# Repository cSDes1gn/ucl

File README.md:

# Automated Under Cabinet Lighting

Modified: 2022-10

Under cabinet lighting (ucl) control system.

## License
This project is licensed under the terms of the [MIT License](LICENSE)

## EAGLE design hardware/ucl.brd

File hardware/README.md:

# EAGLE CAD Files

Modified: 2023-08

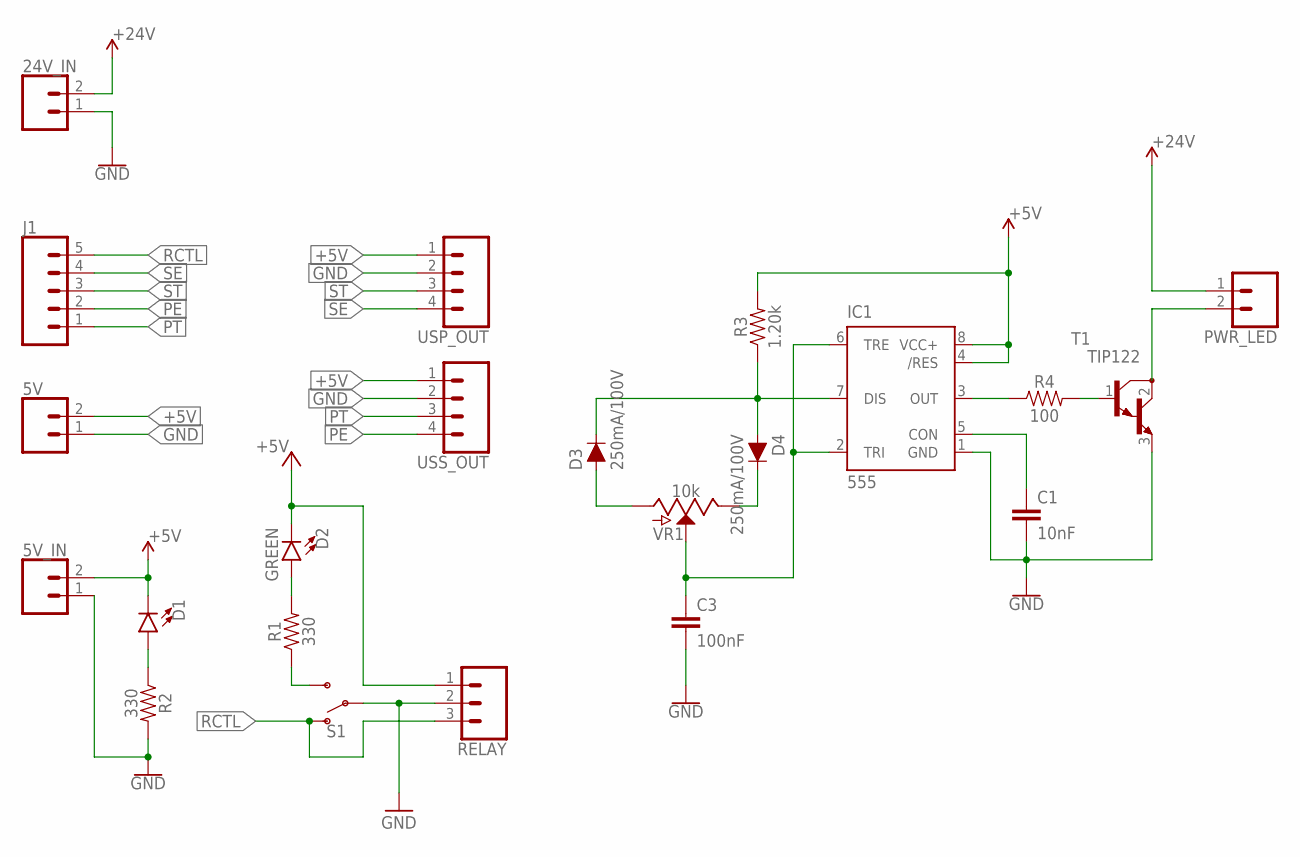
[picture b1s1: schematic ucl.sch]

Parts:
5V: CONN_02POLAR; MOLEX-1X2
5V_IN, 24V_IN: CONN_02POLAR_LOCK; MOLEX-1X2_LOCK
C1: 10nF; 0402-TIGHT
C3: 100nF; 0402-TIGHT
D1: LED1206; LED-1206
D2: GREEN; LED-1206
D3, D4: 250mA/100V; SOD-323
IC1: 555; SO08
J1: CONN_05; 1X05
PWR_LED: CONN_02POLAR_LOCK; MOLEX-1X2_LOCK
R1, R2: 330; 0603
R3: 1.20k; 0603
R4: 100; 0603
RELAY: CONN_03POLAR_LOCK; MOLEX-1X3_LOCK
S1: SWITCH-SPDT-PTH-11.6X4.0MM-KIT; SWITCH_SPDT_PTH_11.6X4.0MM_KIT
T1: TIP122; TO220
USP_OUT: CONN_04POLAR_LOCK; MOLEX-1X4_LOCK
USS_OUT: CONN_04POLAR_LOCK; MOLEX-1X4_LOCK
VR1: 10k; POT-PTH-ALPS

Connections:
+5V: 5V.2, 5V_IN.2, D1.C, D2.C, IC1.4 (/RES), IC1.8 (VCC+), R3.2, RELAY.1, USP_OUT.1, USS_OUT.1
+24V: 24V_IN.2, PWR_LED.1
GND: 5V.1, 5V_IN.1, 24V_IN.1, C1.2, C3.2, IC1.1 (GND), R2.2, RELAY.2, S1.2, T1.3 (E), USP_OUT.2, USS_OUT.2
unnamed: R1.1, S1.3 (S)
unnamed: D2.A, R1.2
unnamed: D1.A, R2.1
unnamed: D3.C, D4.A, IC1.7 (DIS), R3.1
unnamed: D3.A, VR1.P$3 (A)
unnamed: D4.C, VR1.P$1 (E)
unnamed: C3.1, IC1.2 (TRI), IC1.6 (TRE), VR1.P$2 (S)
unnamed: IC1.3 (OUT), R4.1
unnamed: R4.2, T1.1 (B)
unnamed: C1.1, IC1.5 (CON)
unnamed: PWR_LED.2, T1.2 (C)
PE: J1.2, USS_OUT.4
PT: J1.1, USS_OUT.3
RCTL: J1.5, RELAY.3, S1.1 (O)
SE: J1.4, USP_OUT.4
ST: J1.3, USP_OUT.3

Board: 2 copper layers, 22 parts (0 on the bottom side), 19 nets, no tracks yet.

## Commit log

2021-11-01 adding eagle hardware project files
2021-11-01 add arduino src code
2022-09-05 some basic commit
2022-09-06 update gitignore
2022-09-06 c vscode config
2022-09-06 add build and flash instructions
2022-09-06 sample usart program
2022-09-06 use usart 0
2022-09-07 update browse path
2022-09-07 add source file linker
2022-09-07 create first module
2022-09-07 move to include folder
2022-09-07 ignore build artefacts
2022-09-07 basic cmake toolchain for fuse setting and compilation
2022-09-07 updates to firmware
2022-09-07 finish first pass of cmake toolchain development
2022-09-07 fix fuse target
2022-09-09 write basic eeprom driver
2022-09-09 small toolchain fixes
2022-09-09 add guards and fix enable bit checks
2022-09-09 add eeprom test
2022-09-09 hack prints
2022-09-10 add brew installs
2022-09-10 add logger source to toolchain
2022-09-10 adapt merase c logger to work with avr
2022-09-10 deprecate arduino api work
2022-09-10 add usart printlf
2022-09-10 improve function names
2022-09-10 add logging test
2022-09-10 add linker options for full floating point conversion
2022-09-10 simplify logger
2022-09-10 complete floating point conv testing
2022-09-10 fix eeprom write transactions
2022-09-10 update eeprom test
2022-09-10 include io header
2022-09-12 fix formatting
2022-09-12 add avrdude
2022-09-12 update cmake ordering
2022-09-12 remove doxygen define
2022-09-13 add configuration include for general microchip config
2022-09-13 implement 8 bit phase correct PWM stimulus on PL3
2022-09-15 add pwm sweep test
2022-09-15 fix pwm wake
2022-09-15 pwm_wake bitclear
2022-09-16 first pass at rotary encoder driver
2022-09-25 add basic driver testing framework
2022-09-25 group hardware driver modules
2022-09-25 update cmake targets
2022-09-25 move re logic to encoder module
2022-09-25 build out encoder event queue
2022-10-12 refactor cmake to use new style compiler config
2022-10-16 implement encoder table
2022-10-18 remove test methods and complex isr debouncing
2022-10-18 encoder map and ISR PCINT debounce implementation
2022-10-18 finalize re impl
2022-10-18 implement uint8_t circular buffer api
2022-10-18 use circular buffer to store re events
2022-10-18 implement simple buffer digest
2022-10-18 add event clear
2022-10-18 fix buf in empty check
2022-10-18 interrupt and buffer sync
2022-10-30 remove upstream vscode settings
2022-10-30 add dev folder to source control vscode config
2022-10-30 gitignore vscode conf
2022-10-30 implement avr-gcc toolchain
2022-10-30 create a config.h file
2022-10-30 refactor cmake lists to integrate avr-gcc toolchain
2022-10-30 remove delay for bad play with optimization flags
2022-10-30 fix size target
2022-10-30 add build job
2022-10-30 fix pkg
2022-10-30 implement basic clang-format
2022-10-30 use config file to pass F_CPU
2022-10-30 add fcpu def
2022-10-30 deprecate configuration.h
2022-10-30 autoformatting
2022-10-30 fix cache arg
2022-10-30 add clanf-format job
2022-10-30 fix step indents
2022-10-30 add case label indents
2022-10-30 shorten names
2022-10-30 clang-format logger
2022-10-30 clang-format main.c and tests.c
2022-10-30 add avrlibc
2022-10-30 add objdump target
2022-10-30 add objdump
2022-10-30 add pull request template
2022-11-03 openocd testing
2022-11-03 add i2c source
2022-11-03 start i2c driver functions
2022-11-07 i2c driver update
2023-08-24 add ddd
2023-08-24 Added block.drawio
2023-08-24 Added power.drawio
2023-08-28 add hw sim and cad readme
2023-08-28 add power mux sim
2023-12-17 Added ucl-block.drawio

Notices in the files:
parts and their libraries:
SparkFun-Connectors: Licensing: Creative Commons ShareAlike 4.0 International - https://creativecommons.org/licenses/by-sa/4.0
